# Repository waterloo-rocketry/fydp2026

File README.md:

# FYDP 2026 Electrical & Software

Sisyphus is a regeneratively cooled, 3D-printed liquid rocket engine. There are threee main electrical projects that support this system: Automedon, Achilles, and Theseus

## Automedon
Automedon is a repackaging of the team's existing EGSE stack (namely RLCS, DAQ, and GSPD) within two fully enclosed NEMA panels and with a redesigned power architecture. This vastly improves the robustness and utility of the system
Design doc: https://docs.google.com/document/d/1RASc9nuHLxcU_nNqpzqdATsLbMFS-u7HsDOORrnuTvM/edit?tab=t.0#heading=h.aovynwwb2h1r

## Achilles
Achilles, like its namesake, is designed to be an unkillable DAQ module that retains good analog performance. Unlike the team's previous COTS solutions, the system supports up to 30V common mode and differential signals, and is protected up to +/- 60V at the inputs.
DAQ v2 Design Doc (for context): https://docs.google.com/document/d/1antcjPh_7nqCMTjgXxEhXMyPKeuij0gU7g0J603f2qo/edit?tab=t.0#heading=h.4f9eymtkxact

## Theseus
Theseus is the third iteration on the team's integrated propulsion avionics PCB. It is designed to read from pressure transducers, Hall sensors, and RTDs (which are very necessary for regen testing), as well as actuating solenoid valves

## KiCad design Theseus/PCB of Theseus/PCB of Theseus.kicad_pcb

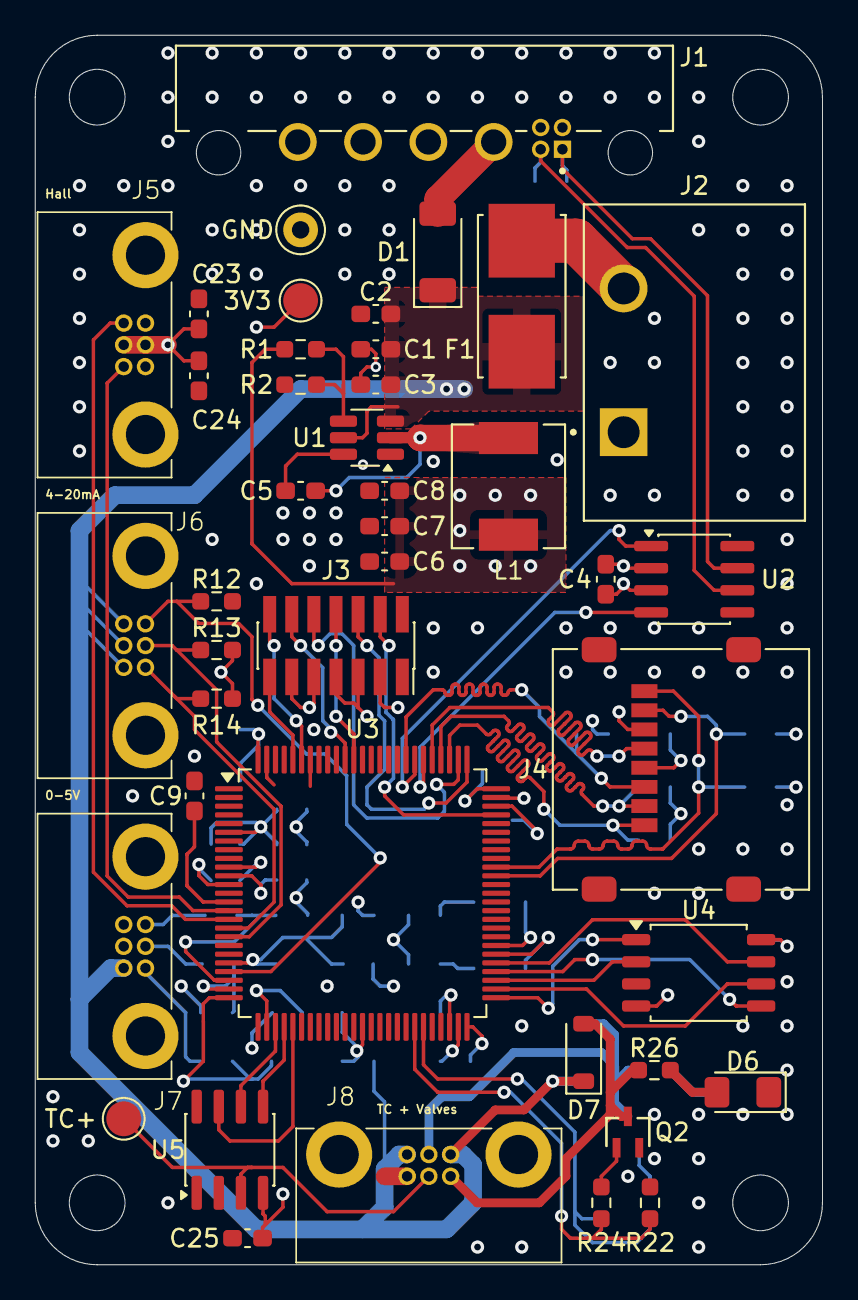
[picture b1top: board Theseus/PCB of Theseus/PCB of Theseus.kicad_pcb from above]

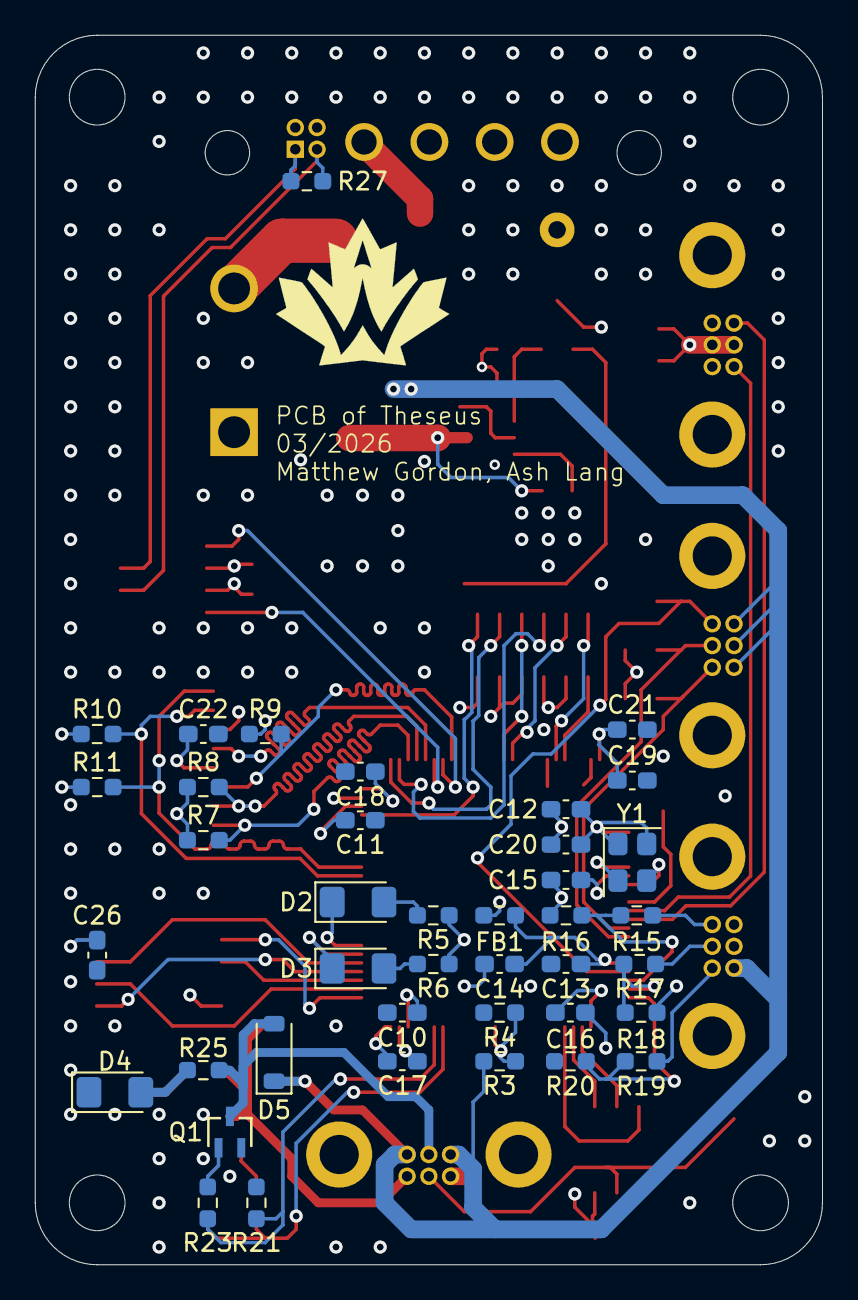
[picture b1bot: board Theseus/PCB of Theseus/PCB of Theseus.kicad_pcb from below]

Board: 4 copper layers, 45.2 x 70.6 mm, 86 parts (40 on the bottom side), 63 nets.

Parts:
3V3: TestPoint; TestPoint_Pad_D2.0mm
C1, C2, C22: 10u; C_0603_1608Metric_Pad1.08x0.95mm_HandSolder
C3, C5, C9, C12, C13, C15, C16, C17, C18, C19, C26: 100n; C_0603_1608Metric_Pad1.08x0.95mm_HandSolder
C4, C23, C24, C25: 0.1u; C_0603_1608Metric_Pad1.08x0.95mm_HandSolder
C6, C7, C8: 22u; C_0603_1608Metric_Pad1.08x0.95mm_HandSolder
C10, C11: 2.2u; C_0603_1608Metric_Pad1.08x0.95mm_HandSolder
C14: 1n; C_0603_1608Metric_Pad1.08x0.95mm_HandSolder
C20: 0.01uF; C_0603_1608Metric_Pad1.08x0.95mm_HandSolder
C21: 4.7u; C_0603_1608Metric_Pad1.08x0.95mm_HandSolder
D1: PMEG3030EP; D_SOD-128
D2: WHITE; LED_1206_3216Metric_Pad1.42x1.75mm_HandSolder
D3: BLUE; LED_1206_3216Metric_Pad1.42x1.75mm_HandSolder
D4, D6: GREEN; LED_1206_3216Metric_Pad1.42x1.75mm_HandSolder
D5, D7: CDBW140-G; D_SOD-123
F1: 0154005.DRL; FUSE_0154005.DR
FB1: PE-0603PFB121ST; R_0603_1608Metric_Pad0.98x0.95mm_HandSolder
GND: TestPoint; TestPoint_Keystone_5000-5004_Miniature
H1, H2, H3, H4: MountingHole; MountingHole_3.2mm_M3_ISO14580
J1: G125-MH104M4-04AD000P; connector_Harwin_G125-MH104M4-04AD000P
J2: 4DB-P108-02
J3: CN4 STDC14 (Programmer); PinSocket_2x07_P1.27mm_Vertical_SMD
J4: Micro SD Holder 0472192001; microSD_HC_Molex_47219-2001
J5, J6, J7, J8: Conn_01x06_Socket; connector_Harwin_G125–MG10605M4P
L1: SPM6530T-2R2M; IND_SPM6530T-2R2M
Q1, Q2: DMG1012UW-7; SOT_12UW-7_DIO
R1: 33.2k; R_0603_1608Metric_Pad0.98x0.95mm_HandSolder
R2: 10k; R_0603_1608Metric_Pad0.98x0.95mm_HandSolder
R3: 300K; R_0603_1608Metric_Pad0.98x0.95mm_HandSolder
R4: 100K; R_0603_1608Metric_Pad0.98x0.95mm_HandSolder
R5, R6: 169R; R_0603_1608Metric_Pad0.98x0.95mm_HandSolder
R7, R8, R9, R10, R11: 51k; R_0603_1608Metric_Pad0.98x0.95mm_HandSolder
R12, R13, R14: 150R ±0.1%; R_0603_1608Metric_Pad0.98x0.95mm_HandSolder
R15, R17, R19: 82K; R_0603_1608Metric_Pad0.98x0.95mm_HandSolder
R16, R18, R20: 130K; R_0603_1608Metric_Pad0.98x0.95mm_HandSolder
R21, R22: 150k; R_0603_1608Metric_Pad0.98x0.95mm_HandSolder
R23, R24: 100R; R_0603_1608Metric_Pad0.98x0.95mm_HandSolder
R25, R26: 649R; R_0603_1608Metric_Pad0.98x0.95mm_HandSolder
R27: 120R; R_0603_1608Metric_Pad0.98x0.95mm_HandSolder
TC+: TC1+; TestPoint_Pad_D2.0mm
U1: TPS565201DDC; SOT-23-6_Handsoldering
U2: TCAN334; SOIC-8_3.9x4.9mm_P1.27mm
U3: STM32H750VBTx; LQFP-100_14x14mm_P0.5mm
U4: MX25L25645G; SOIC-8_5.3x5.3mm_P1.27mm
U5: MAX6675; SOIC-8_3.9x4.9mm_P1.27mm
Y1: ASE-4.000MHz-L-C-T; Oscillator_SMD_Abracon_ASE-4Pin_3.2x2.5mm

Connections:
+3.3V: 3V3.1, C4.1, C6.1, C7.1, C8.1, C12.1, C15.1, C16.1, C17.1, C18.1, C19.1, C20.1, C21.1, C22.1, C23.1, C24.1, C25.1, C26.1, FB1.1, J3.3, J4.4 (VDD), J5.2, J5.5, L1.1, R1.1, R5.1, R6.1, R7.1, R8.1, R9.1, R10.1, R11.1, U2.3 (VCC), U3.6 (VBAT), U3.11 (VDD), U3.27 (VDD), U3.50 (VDD), U3.75 (VDD), U3.100 (VDD), U4.8 (VCC), U5.4 (Vcc), Y1.1 (EN), Y1.4 (Vdd)
+BATT: C1.1, C2.1, C3.1, D1.1 (K), D5.1 (K), D7.1 (K), F1.1, J6.4, J6.5, J6.6, J7.4, J8.1, J8.3, R3.1, U1.3 (VIN), U1.5 (EN)
/CANH: J1.1 (CANH), R27.1, U2.7 (CANH)
/CANL: J1.2 (CANL), R27.2, U2.6 (CANL)
/CAN_Rx: U2.4 (RXD), U3.81 (PD0)
/CAN_Tx: U2.1 (TXD), U3.82 (PD1)
/MCU/FLASH_MISO: U3.53 (PB14), U4.2 (SO/SIO1)
/MCU/FLASH_MOSI: U3.54 (PB15), U4.5 (SI/SIO0)
/MCU/FLASH_SCK: U3.52 (PB13), U4.6 (SCLK)
/MCU/HALL_1: J5.4, U3.15 (PC0)
/MCU/HALL_2: J5.6, U3.16 (PC1)
/MCU/LED_B: D3.1 (K), U3.56 (PD9)
/MCU/LED_W: D2.1 (K), U3.57 (PD10)
/MCU/OSC_IN: U3.12 (PH0), Y1.3 (OUT)
/MCU/PT4: R19.2, R20.1, U3.25 (PA3)
/MCU/PT5: R17.2, R18.1, U3.24 (PA2)
/MCU/PT6: R15.2, R16.1, U3.23 (PA1)
/MCU/SD_CLK: J4.5 (CLK), U3.80 (PC12)
/MCU/SD_CMD: J4.3 (CMD), R9.2, U3.83 (PD2)
/MCU/SD_D0: J4.7 (DAT0), R10.2, U3.65 (PC8)
/MCU/SD_D1: J4.8 (DAT1), R11.2, U3.66 (PC9)
/MCU/SD_D2: J4.1 (DAT2), R7.2, U3.78 (PC10)
/MCU/SD_D3: J4.2 (DAT3/CD), R8.2, U3.79 (PC11)
/MCU/TC1_MISO: U3.30 (PA6), U5.7 (SO)
/MCU/TC1_SCK: U3.29 (PA5), U5.5 (SCK)
/MCU/TCK: J3.6, U3.76 (PA14)
/MCU/TDI: J3.10, U3.77 (PA15)
/MCU/TDO: J3.8, U3.89 (PB3)
/MCU/TMS: J3.4, U3.72 (PA13)
/MCU/TRST: J3.12, U3.90 (PB4)
/MCU/VALVE_1: R21.2, R23.2, U3.45 (PE15)
/MCU/VALVE_2: R22.1, R24.2, U3.44 (PE14)
/MCU/VCP_RX: J3.13, U3.96 (PB9)
/MCU/VCP_TX: J3.14, U3.95 (PB8)
/MCU/VDDA: C13.1, C14.1, FB1.2, U3.21 (VDDA)
/MCU/V_BATT: R3.2, R4.1, U3.38 (PE8)
/MCU/~FLASH_CS: U3.51 (PB12), U4.1 (CS#)
/MCU/~FLASH_RESET: U3.55 (PD8), U4.7 (RESET#/SIO3)
/MCU/~TC1_CS: U3.28 (PA4), U5.6 (~CS)
/Valves and Sensors/PT1_OUT: J6.1, R14.1, U3.17 (PC2_C)
/Valves and Sensors/PT2_OUT: J6.2, R13.1, U3.18 (PC3_C)
/Valves and Sensors/PT3_OUT: J6.3, R12.1, U3.22 (PA0)
/Valves and Sensors/PT4_OUT: J7.1, R19.1
/Valves and Sensors/PT5_OUT: J7.2, R17.1
/Valves and Sensors/PT6_OUT: J7.3, R15.1
/Valves and Sensors/TC1+: J8.5, TC+.1, U5.3 (T+)
GND: C1.2, C2.2, C3.2, C4.2, C6.2, C7.2, C8.2, C9.2, C10.2, C11.2, C12.2, C13.2, C14.2, C15.2, C16.2, C17.2, C18.2, C19.2, C20.2, C21.2, C22.2, C23.2, C24.2, C25.2, C26.2, D4.1 (K), D6.1 (K), GND.1, J1.D (GND), J2.1, J3.5, J3.7, J3.9, J3.11, J4.6 (VSS), J4.9 (SHIELD), J5.1, J5.3, J7.6, J8.6, Q1.2 (S), Q2.2 (S), R2.2, R4.2, R12.2, R13.2, R14.2, R16.2, R18.2, R20.2, R21.1, R22.2, U1.1 (GND), U2.2 (GND), U2.5 (SHDN), U2.8 (STB), U3.10 (VSS), U3.19 (VSSA), U3.26 (VSS), U3.49 (VSS), U3.74 (VSS), U3.94 (BOOT0), U3.99 (VSS), U4.4 (GND), U5.1 (GND), U5.2 (T-), Y1.2 (GND)
unnamed: C10.1, U3.48 (VCAP)
unnamed: C11.1, U3.73 (VCAP)
unnamed: D1.2 (A), J1.A (+CHG)
unnamed: D2.2 (A), R5.2
unnamed: D3.2 (A), R6.2
unnamed: D4.2 (A), R25.1
unnamed: D5.2 (A), J8.2, Q1.3 (D), R25.2
unnamed: D6.2 (A), R26.2
unnamed: D7.2 (A), J8.4, Q2.3 (D), R26.1
unnamed: F1.2, J2.2
unnamed: Q1.1 (G), R23.1
unnamed: Q2.1 (G), R24.1
unnamed: C5.1, L1.2, U1.2 (SW)
unnamed: C5.2, U1.6 (VBST)
unnamed: R1.2, R2.1, U1.4 (VFB)
unnamed: C9.1, U3.14 (NRST)

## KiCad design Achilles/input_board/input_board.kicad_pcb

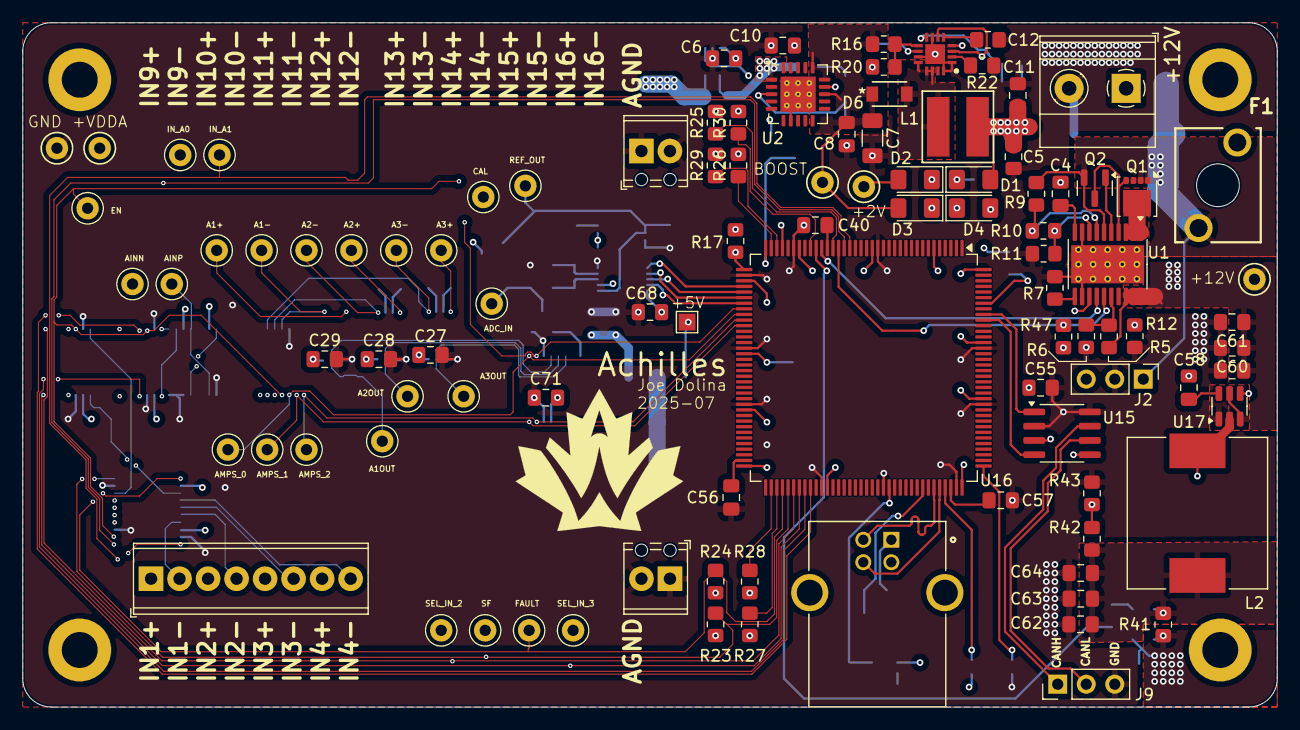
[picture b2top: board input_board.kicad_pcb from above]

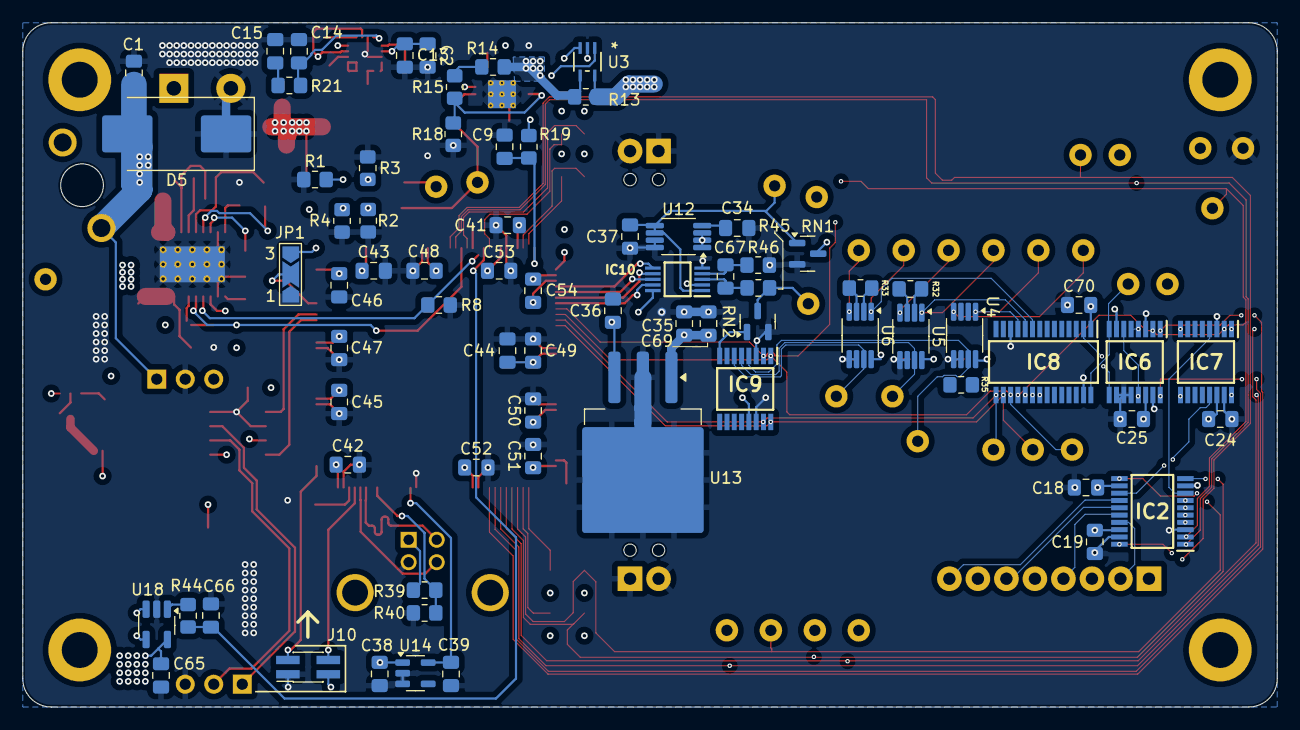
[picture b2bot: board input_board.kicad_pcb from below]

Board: 6 copper layers, 111.8 x 61.0 mm, 177 parts (73 on the bottom side), 114 nets.

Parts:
C1, C59, C60: 10uF; C_0805_2012Metric_Pad1.18x1.45mm_HandSolder
C2, C4, C13: 10nF; C_0805_2012Metric_Pad1.18x1.45mm_HandSolder
C5: 4.7uF; C_0805_2012Metric_Pad1.18x1.45mm_HandSolder
C6, C10, C12, C19, C34, C37, C38, C65, C68, C69: 1uF; C_0805_2012Metric_Pad1.18x1.45mm_HandSolder
C7: 4.7uF; C_1206_3216Metric_Pad1.33x1.80mm_HandSolder
C8, C11, C58, C61: 100nF; C_0805_2012Metric_Pad1.18x1.45mm_HandSolder
C9, C66: 1.6uF; C_0805_2012Metric_Pad1.18x1.45mm_HandSolder
C14: 300pF; C_0805_2012Metric_Pad1.18x1.45mm_HandSolder
C15: 6.8nF; C_0805_2012Metric_Pad1.18x1.45mm_HandSolder
C18, C24, C25, C27, C28, C29, C36, C70, C71: 0.1uF; C_0805_2012Metric_Pad1.18x1.45mm_HandSolder
C35: 0.33uF; C_0805_2012Metric_Pad1.18x1.45mm_HandSolder
C39: 2.2uF; C_0805_2012Metric_Pad1.18x1.45mm_HandSolder
C40, C43, C44, C45, C46, C47, C48, C49, C50, C51, C52, C53, C54: 100n; C_0805_2012Metric_Pad1.18x1.45mm_HandSolder
C41: 1u; C_0805_2012Metric_Pad1.18x1.45mm_HandSolder
C42: 4.7u; C_0805_2012Metric_Pad1.18x1.45mm_HandSolder
C55: 10u; C_0805_2012Metric_Pad1.18x1.45mm_HandSolder
C56, C57: 2.2u; C_0805_2012Metric_Pad1.18x1.45mm_HandSolder
C62, C63, C64: 22uF; C_0805_2012Metric_Pad1.18x1.45mm_HandSolder
C67: 1.1nF; C_0805_2012Metric_Pad1.18x1.45mm_HandSolder
D1: BLUE; LED_1206_3216Metric_Pad1.42x1.75mm_HandSolder
D2: GREEN; LED_1206_3216Metric_Pad1.42x1.75mm_HandSolder
D3: RED; LED_1206_3216Metric_Pad1.42x1.75mm_HandSolder
D4: WHITE; LED_1206_3216Metric_Pad1.42x1.75mm_HandSolder
D5: SMCJ36CA; D_SMC_Handsoldering
D6: B260S1F-7; CR_SOD123F_DIO
F1: 5A; 01530009Z
H1, H2, H3, H4: MountingHole_Pad; MountingHole_3.2mm_M3_DIN965_Pad
IC1: LM5157RTER; QFN50P300X300X80-17N-D
IC2: TMUX7349FPWR; SOP65P640X120-20N
IC6, IC7: MUX509IPW; SOP65P640X120-16N
IC8: MUX36D08IPW; SOP65P640X120-28N
IC9: MUX508IPW; SOP65P640X120-16N
IC10: ADS8860IDGSR; SOP50P490X110-10N
J1: Screw_Terminal_01x02; TerminalBlock_Phoenix_MKDS-1,5-2-5.08_1x02_P5.08mm_Horizont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
J2: Screw_Terminal_01x03; PinHeader_1x03_P2.54mm_Vertical
J3: Screw_Terminal_01x08; TerminalBlock_Phoenix_MPT-0,5-8-2.54_1x08_P2.54mm_Horizontal
J7, J11: Screw_Terminal_01x02; TerminalBlock_Phoenix_MPT-0,5-2-2.54_1x02_P2.54mm_Horizontal
J8: USB_B; CUI_UJ2-BH-1-TH
J9: CAN; PinHeader_1x03_P2.54mm_Vertical
J10: Programmer; PinSocket_2x02_P1.27mm_Vertical_SMD
JP1: Jumper_3_Open; SolderJumper-3_P2.0mm_Open_TrianglePad1.0x1.5mm_NumberLabels
L1: SRR5018-3R9Y; IND_BOURNS_SRR5018
L2: SRP1265A-2R2M; IND_SRP1265A-2R2M
Q1: CSD19537Q3; VSON-8_3.3x3.3mm_P0.65mm_NexFET
Q2: BSS138; SOT-23
R1: 510R; R_0805_2012Metric_Pad1.20x1.40mm_HandSolder
R2: 1.3kR; R_0805_2012Metric_Pad1.20x1.40mm_HandSolder
R3: 150R; R_0805_2012Metric_Pad1.20x1.40mm_HandSolder
R4, R19, R44: 500R; R_0805_2012Metric_Pad1.20x1.40mm_HandSolder
R5: 435kR; R_0805_2012Metric_Pad1.20x1.40mm_HandSolder
R6: 56kR; R_0805_2012Metric_Pad1.20x1.40mm_HandSolder
R7: 9.09kR; R_0805_2012Metric_Pad1.20x1.40mm_HandSolder
R8: 38.3kR; R_0805_2012Metric_Pad1.20x1.40mm_HandSolder
R9: 374kR; R_0805_2012Metric_Pad1.20x1.40mm_HandSolder
R10: 17kR; R_0805_2012Metric_Pad1.20x1.40mm_HandSolder
R11: 34kR; R_0805_2012Metric_Pad1.20x1.40mm_HandSolder
R12, R17, R18, R43, R47: 10kR; R_0805_2012Metric_Pad1.20x1.40mm_HandSolder
R13, R41: 20mR; R_0805_2012Metric_Pad1.20x1.40mm_HandSolder
R14: 203kR; R_0805_2012Metric_Pad1.20x1.40mm_HandSolder
R15: 1.29kR; R_0805_2012Metric_Pad1.20x1.40mm_HandSolder
R16: 75kR; R_0805_2012Metric_Pad1.20x1.40mm_HandSolder
R20: 2.43kR; R_0805_2012Metric_Pad1.20x1.40mm_HandSolder
R21: 1.33k; R_0805_2012Metric_Pad1.20x1.40mm_HandSolder
R22: 9.76kR; R_0805_2012Metric_Pad1.20x1.40mm_HandSolder
R23, R24, R25, R26, R27, R28, R29, R30: 1kR; R_0805_2012Metric_Pad1.20x1.40mm_HandSolder
R32: 6kR; R_0805_2012Metric_Pad1.20x1.40mm_HandSolder
R33: 1.2kR; R_0805_2012Metric_Pad1.20x1.40mm_HandSolder
R35: 122R; R_0805_2012Metric_Pad1.20x1.40mm_HandSolder
R39: 51kR; R_0805_2012Metric_Pad1.20x1.40mm_HandSolder
R40: 24kR; R_0805_2012Metric_Pad1.20x1.40mm_HandSolder
R42: 17.4kR; R_0805_2012Metric_Pad1.20x1.40mm_HandSolder
R45, R46: 15R; R_0805_2012Metric_Pad1.20x1.40mm_HandSolder
RN1: MAX5490GA01000-T; SOT-23
RN2: MAX5490TA05000-T; SOT-23
TP1: 12V; TestPoint_Keystone_5000-5004_Miniature
TP2: VBOOST; TestPoint_Keystone_5000-5004_Miniature
TP3: 2V; TestPoint_Keystone_5000-5004_Miniature
TP4: 5V; TestPoint_Pad_1.5x1.5mm
TP5: VDDA; TestPoint_Keystone_5000-5004_Miniature
TP6: GND; TestPoint_Keystone_5000-5004_Miniature
TP7: A1_OUT; TestPoint_Keystone_5000-5004_Miniature
TP8: AMP1-; TestPoint_Keystone_5000-5004_Miniature
TP9: AMP1+; TestPoint_Keystone_5000-5004_Miniature
TP10: AMP2-; TestPoint_Keystone_5000-5004_Miniature
TP11: AMP2+; TestPoint_Keystone_5000-5004_Miniature
TP12: A2_OUT; TestPoint_Keystone_5000-5004_Miniature
TP13: AMP3-; TestPoint_Keystone_5000-5004_Miniature
TP14: AMP3+; TestPoint_Keystone_5000-5004_Miniature
TP15: A3_OUT; TestPoint_Keystone_5000-5004_Miniature
TP16: REF_OUT; TestPoint_Keystone_5000-5004_Miniature
TP17: CAL; TestPoint_Keystone_5000-5004_Miniature
TP18: AINP; TestPoint_Keystone_5000-5004_Miniature
TP19: IN_A0; TestPoint_Keystone_5000-5004_Miniature
TP20: IN_A1; TestPoint_Keystone_5000-5004_Miniature
TP21: SF_1..4; TestPoint_Keystone_5000-5004_Miniature
TP22: FF_1..4; TestPoint_Keystone_5000-5004_Miniature
TP23: EN; TestPoint_Keystone_5000-5004_Miniature
TP24: AMPS0; TestPoint_Keystone_5000-5004_Miniature
TP25: AMPS1; TestPoint_Keystone_5000-5004_Miniature
TP26: AMPS2; TestPoint_Keystone_5000-5004_Miniature
TP27, TP28: AMPIN-; TestPoint_Keystone_5000-5004_Miniature
TP29: SEL_IN_2; TestPoint_Keystone_5000-5004_Miniature
TP30: SEL_IN_3; TestPoint_Keystone_5000-5004_Miniature
U1: TPS26631PWP; HTSSOP-20-1EP_4.4x6.5mm_P0.65mm_EP3.4x6.5mm_Mask2.96x2.96mm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
U2: TPS7A4701xRGW; Texas_RGW0020A_VQFN-20-1EP_5x5mm_P0.65mm_EP3.15x3.15mm_Ther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
U3: INA290A3; SC70-5_DCK_TEX
U4, U5, U6: INA849DGK; VSSOP-8_3x3mm_P0.65mm
U12: REF6050xDGK; VSSOP-8_3x3mm_P0.65mm
U13: uA7805; TO-263-3_TabPin2
U14: TPS76933; SOT-23-5
U15: MCP2562; SOIC-8_3.9x4.9mm_P1.27mm
U16: STM32H750ZBTx; LQFP-144_20x20mm_P0.5mm
U17: TPS565201; SOT-23-6
U18: INA180A3; SOT-23-5_HandSoldering

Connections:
+2V: C6.1, C41.1, C42.1, C43.1, C44.1, C45.1, C46.1, C47.1, C48.1, C49.1, C50.1, C51.1, C52.1, C53.1, C54.1, C65.1, C68.2, D3.2 (A), IC10.10 (DVDD), J10.2, JP1.3 (B), R17.1, R23.2, R24.2, R25.2, R26.2, R27.2, R28.2, R29.2, R30.2, R41.2, R47.1, TP3.1, U3.3 (VS), U15.5 (VIO), U16.6 (VBAT), U16.17 (VDD), U16.30 (VDD), U16.33 (VDDA), U16.39 (VDD), U16.52 (VDD), U16.62 (VDD), U16.72 (VDD), U16.84 (VDD), U16.108 (VDD), U16.121 (VDD), U16.131 (VDD), U16.144 (VDD), U18.4 (IN-), U18.5 (VS)
+3V3: C39.1, U14.5 (OUT), U16.95 (VDD33_USB)
+5V: C36.1, C55.1, D4.2 (A), TP4.1, U12.1 (VIN), U12.2 (EN), U12.3 (SS), U13.3 (OUT), U15.3 (VDD)
+12V: C5.1, C11.1, C38.1, C59.1, C60.1, C61.1, D1.2 (A), IC1.3 (BIAS), IC1.6 (EN/UVLO/SYNC), L1.1, R5.1, TP1.1, U1.18 (OUT), U1.19 (OUT), U1.20 (OUT), U14.1 (IN), U17.3 (VIN), U17.5 (EN)
/2V DVCC/BST: C58.2, U17.6 (VBST)
/2V DVCC/ISENSE_2V: C66.1, R44.1, U16.27 (PC1)
/12V Input/IN_SYS: C1.1, D5.2 (A2), F1.2, J2.1, Q1.1 (S), Q1.2 (S), Q1.3 (S), Q2.2 (S), R9.1, U1.6 (IN_SYS)
/12V Input/ISENSE_12V: R8.1, U1.14 (IMON), U16.26 (PC0)
/12V Input/PGTH: R5.2, R6.1, U1.16 (PGTH)
/12V Input/PWR_ON: J2.3, R12.1, U1.13 (~SHDN)
/12V Input/V_OVP: R10.2, R11.1, U1.8 (OVP)
/12V Input/V_UVLO: R9.2, R10.1, U1.7 (UVLO)
/12V Input/~FLT_12V: R47.2, U1.15 (~FLT), U16.23 (PH0)
/30V VDDA/ISENSE_30V: C9.1, R19.1, U16.36 (PA2)
/30V VDDA/PGOOD_30V: IC1.4 (PGOOD), R17.2, U16.37 (PA3)
/ADC + FVR/ADC_IN: IC9.8 (D), RN2.1 (COM1)
/ADC + FVR/CAL: IC6.7 (S4A), RN1.3 (R2), TP17.1
/ADC + FVR/CONVST: IC10.6 (CONVST), U16.40 (PA4)
/ADC + FVR/MISO: IC10.7 (DOUT), U16.42 (PA6)
/ADC + FVR/MOSI: IC10.9 (DIN), U16.43 (PA7)
/ADC + FVR/REF_OUT: C37.2, IC10.1 (REF), RN1.1 (COM1), TP16.1, U12.5 (OUT_S), U12.6 (OUT_F)
/ADC + FVR/SCK: IC10.8 (SCLK), U16.41 (PA5)
/Amplifiers/A1_OUT: IC9.4 (S1), TP7.1, U4.7
/Amplifiers/A2_OUT: IC9.5 (S2), TP12.1, U5.7
/Amplifiers/A3_OUT: IC9.6 (S3), TP15.1, U6.7
/Amplifiers/AMP1+: IC8.19 (S1A), TP9.1, U4.4 (+)
/Amplifiers/AMP1-: IC8.11 (S1B), TP8.1, U4.1 (-)
/Amplifiers/AMP2+: IC8.20 (S2A), TP11.1, U5.4 (+)
/Amplifiers/AMP2-: IC8.10 (S2B), TP10.1, U5.1 (-)
/Amplifiers/AMP3+: IC8.21 (S3A), TP14.1, U6.4 (+)
/Amplifiers/AMP3-: IC8.9 (S3B), TP13.1, U6.1 (-)
/Amplifiers/AMP_IN+: IC6.8 (DA), IC8.28 (DA), TP28.1
/Amplifiers/AMP_IN-: IC6.9 (DB), IC8.2 (DB), TP27.1
/Amplifiers/AMP_SEL_0: IC8.17 (A0), IC9.1 (A0), TP24.1, U16.45 (PC5)
/Amplifiers/AMP_SEL_1: IC8.16 (A1), IC9.16 (A1), TP25.1, U16.47 (PB1)
/Amplifiers/AMP_SEL_2: IC8.15 (A2), IC9.15 (A2), TP26.1, U16.46 (PB0)
/Frontend/EN_1..4: IC2.2 (EN), IC6.2 (EN), IC7.2 (EN), IC8.18 (EN), IC9.2 (EN), TP23.1, U16.44 (PC4)
/Frontend/FAULT_1..4: IC2.11 (FF), R24.1, TP22.1, U16.76 (PB15)
/Frontend/FAULT_5..8: R28.1, U16.74 (PB13)
/Frontend/FAULT_9..12: R26.1, U16.35 (PA1)
/Frontend/FAULT_13..16: R30.1, U16.28 (PC2_C)
/Frontend/IN1+: IC2.4 (S1A), J3.1
/Frontend/IN1-: IC2.17 (S1B), J3.2
/Frontend/IN2+: IC2.5 (S2A), J3.3
/Frontend/IN2-: IC2.16 (S2B), J3.4
/Frontend/IN3+: IC2.6 (S3A), J3.5
/Frontend/IN3-: IC2.15 (S3B), J3.6
/Frontend/IN4+: IC2.7 (S4A), J3.7
/Frontend/IN4-: IC2.14 (S4B), J3.8
/Frontend/IN+: IC6.4 (S1A), IC6.5 (S2A), IC7.8 (DA)
/Frontend/IN-: IC6.6 (S3A), IC6.13 (S1B), IC7.9 (DB)
/Frontend/INPUT_A0: IC2.1 (A0), TP19.1, U16.22 (PF10)
/Frontend/INPUT_A1: IC2.20 (A1), TP20.1, U16.21 (PF9)
/Frontend/IN_1..4+: IC2.8 (DA), IC7.4 (S1A)
/Frontend/IN_1..4-: IC2.13 (DB), IC7.13 (S1B)
/Frontend/SEL_IN_2: IC7.1 (A0), TP29.1, U16.78 (PD9)
/Frontend/SEL_IN_3: IC7.16 (A1), TP30.1, U16.79 (PD10)
/Frontend/SF_1..4: IC2.10 (SF), R23.1, TP21.1, U16.77 (PD8)
/Frontend/SF_5..8: R27.1, U16.75 (PB14)
/Frontend/SF_9..12: R25.1, U16.24 (PH1)
/Frontend/SF_13..16: R29.1, U16.34 (PA0)
/Frontend/SINGLE_DIFF_0: IC6.1 (A0), U16.81 (PD12)
/Frontend/SINGLE_DIFF_1: IC6.16 (A1), U16.80 (PD11)
/MCU/CAN_RX: U15.4 (RXD), U16.135 (PB5)
/MCU/CAN_TX: U15.1 (TXD), U16.136 (PB6)
/MCU/SWCLK: J10.3, U16.109 (PA14)
/MCU/SWDIO: J10.4, U16.105 (PA13)
/MCU/USB_D+: J8.3 (D+), U16.104 (PA12)
/MCU/USB_D-: J8.2 (D-), U16.103 (PA11)
/MCU/VBUS: J8.1 (VBUS), R39.1
/MCU/VBUS_SENSE: R39.2, R40.1, U16.101 (PA9)
GND: C1.2, C2.2, C4.2, C5.2, C6.2, C7.2, C8.2, C9.2, C10.2, C11.2, C12.2, C13.2, C14.2, C15.2, C18.2, C19.2, C24.2, C25.2, C27.2, C28.2, C29.2, C34.1, C35.2, C36.2, C37.1, C38.2, C39.2, C40.2, C41.2, C42.2, C43.2, C44.2, C45.2, C46.2, C47.2, C48.2, C49.2, C50.2, C51.2, C52.2, C53.2, C54.2, C55.2, C56.2, C57.2, C59.2, C60.2, C61.2, C62.2, C63.2, C64.2, C65.2, C66.2, C68.1, C69.1, C70.1, C71.1, D5.1 (A1), IC1.1 (PGND_1), IC1.7 (AGND), IC1.11 (MODE), IC1.16 (PGND_2), IC1.17 (EP), IC2.3 (VSS), IC2.9 (VFN), IC2.19 (GND), IC6.3 (VSS), IC6.10 (S4B), IC6.11 (S3B), IC6.12 (S2B), IC6.15 (GND), IC7.3 (VSS), IC7.15 (GND), IC8.12 (GND), IC8.27 (VSS), IC9.3 (VSS), IC9.14 (GND), IC10.5 (GND), J1.2, J2.2, J7.1, J7.2, J8.4 (GND), J9.3, J10.1, J11.1, J11.2, JP1.1 (A), R1.2, R2.2, R3.2, R4.2, R6.2, R7.2, R8.2, R11.2, R12.2, R18.2, R20.2, R22.1, R40.2, R43.2, R46.2, RN1.2 (R1), RN2.2 (R1), TP6.1, U1.9 (GND), U1.12 (MODE), U1.21 (GND), U2.7 (GND), U2.21 (EP), U3.2 (GND), U4.5 (Vs-), U4.6 (Ref), U5.5 (Vs-), U5.6 (Ref), U6.5 (Vs-), U6.6 (Ref), U12.7 (GND_F), U12.8 (GND_S), U13.2 (GND), U14.2 (GND), U14.3 (~EN), U15.2 (VSS), U15.8 (STBY), U16.16 (VSS), U16.31 (VSSA), U16.38 (VSS), U16.51 (VSS), U16.61 (VSS), U16.83 (VSS), U16.94 (VSS), U16.107 (VSS), U16.120 (VSS), U16.130 (VSS), U17.1 (GND), U18.2 (GND)
unnamed: C15.1, R21.1
unnamed: C56.1, U16.71 (VCAP)
unnamed: C57.1, U16.106 (VCAP)
unnamed: D1.1 (K), R1.1
unnamed: D2.1 (K), R2.1
unnamed: D3.1 (K), R3.1
unnamed: D4.1 (K), R4.1
unnamed: D6.2 (A), IC1.12 (SW_1), IC1.13 (SW_2), IC1.14 (SW_3), L1.2
unnamed: C14.1, IC1.8 (COMP), R21.2
unnamed: IC1.9 (FB), R16.2, R20.1
unnamed: IC1.5 (RT), R22.2
unnamed: C2.1, C13.1, IC1.10 (SS)
unnamed: C12.1, IC1.2 (VCC)
unnamed: C67.1, IC10.4 (AINN), R46.1
unnamed: C67.2, IC10.3 (AINP), R45.2
unnamed: F1.1, J1.1
unnamed: J9.1, U15.7 (CANH)
unnamed: J9.2, U15.6 (CANL)
unnamed: JP1.2 (C), U16.138 (BOOT0)
unnamed: Q1.5 (D), U1.1 (IN), U1.2 (IN), U1.3 (IN)
unnamed: Q1.4 (G), Q2.3 (D), U1.4 (B_GATE)
unnamed: Q2.1 (G), U1.5 (DRV)
unnamed: R14.2, R15.1
unnamed: R32.1, U5.2 (Rg)
unnamed: R32.2, U5.3 (Rg)
unnamed: R33.1, U6.2 (Rg)
unnamed: R33.2, U6.3 (Rg)
unnamed: R45.1, RN2.3 (R2), TP18.1
unnamed: R7.1, U1.11 (ILIM)
unnamed: C4.1, U1.10 (dVdT)
unnamed: C10.1, U2.14 (NR)
unnamed: R15.2, R18.1, U2.3 (SENSE/FB)
unnamed: R13.1, R14.1, U2.1 (OUT), U2.20 (OUT), U3.4 (IN+)
unnamed: R19.2, U3.1 (VO)
unnamed: C34.2, U12.4 (FILT)
unnamed: C40.1, U16.25 (NRST)
unnamed: C58.1, L2.1, U17.2 (SW)
unnamed: R42.2, R43.1, U17.4 (VFB)
unnamed: C62.1, C63.1, C64.1, L2.2, R41.1, R42.1, U18.3 (IN+)
unnamed: R44.2, U18.1 (VO)
VDDA: C18.1, C19.1, C24.1, C25.1, C27.1, C28.1, C29.1, C35.1, C69.2, C70.2, C71.2, IC2.12 (VFP), IC2.18 (VDD), IC6.14 (VDD), IC7.14 (VDD), IC8.1 (VDD), IC9.13 (VDD), IC10.2 (AVDD), R13.2, TP5.1, U3.5 (IN-), U4.8 (Vs+), U5.8 (Vs+), U6.8 (Vs+), U13.1 (IN)
V_BOOST: C7.1, C8.1, D2.2 (A), D6.1 (K), R16.1, TP2.1, U2.13 (EN), U2.15 (IN), U2.16 (IN)

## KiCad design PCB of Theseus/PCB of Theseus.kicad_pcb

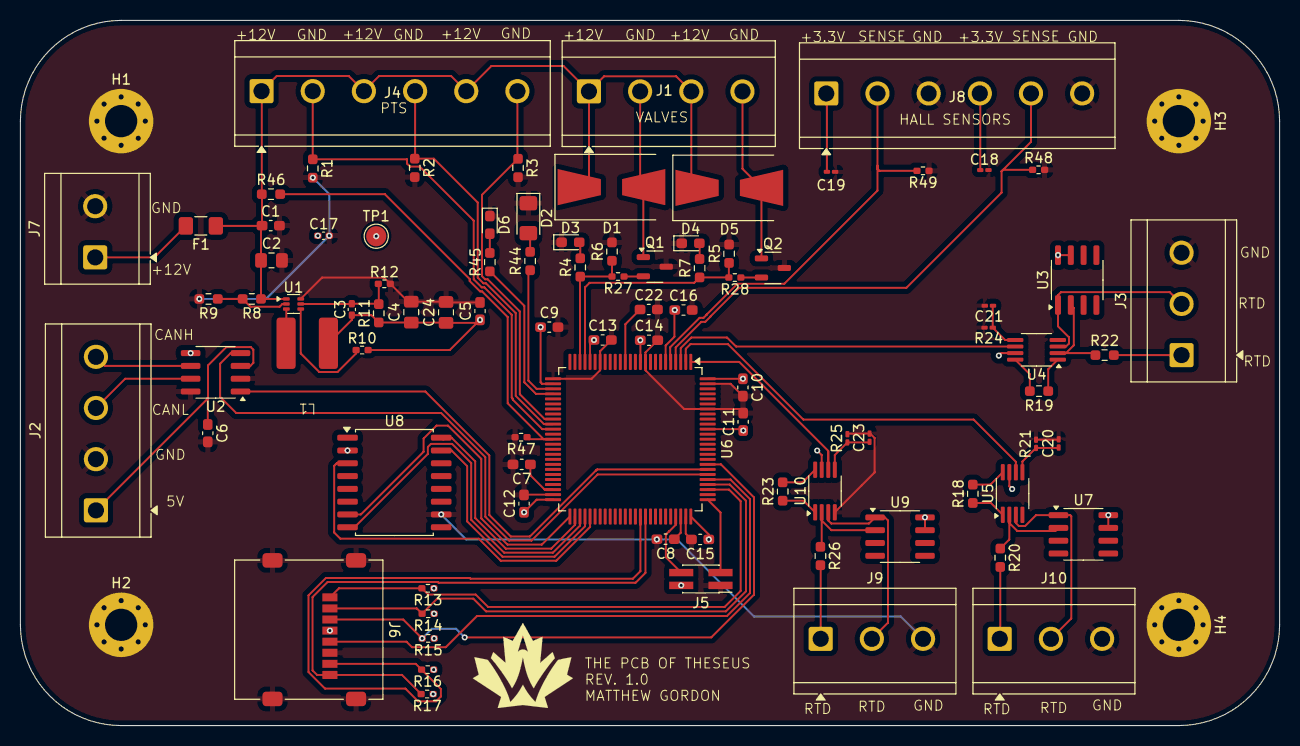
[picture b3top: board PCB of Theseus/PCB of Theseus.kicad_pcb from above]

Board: 2 copper layers, 125.0 x 70.0 mm, 93 parts (0 on the bottom side), 68 nets.

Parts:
C1, C5: 100nF; C_0603_1608Metric_Pad1.08x0.95mm_HandSolder
C2, C4, C24: 22uF; C_0805_2012Metric_Pad1.18x1.45mm_HandSolder
C3: 10pF; C_0402_1005Metric_Pad0.74x0.62mm_HandSolder
C6: 10u; C_0603_1608Metric_Pad1.08x0.95mm_HandSolder
C7, C8: 2.2u; C_0603_1608Metric_Pad1.08x0.95mm_HandSolder
C9, C10, C11, C12, C13, C14, C15, C22: 100n; C_0603_1608Metric_Pad1.08x0.95mm_HandSolder
C16: 4.7u; C_0603_1608Metric_Pad1.08x0.95mm_HandSolder
C17: 1u; C_0402_1005Metric_Pad0.74x0.62mm_HandSolder
C18, C19: 0.1uF; C_0201_0603Metric_Pad0.64x0.40mm_HandSolder
C20, C21, C23: 510pF; C_0201_0603Metric_Pad0.64x0.40mm_HandSolder
D1, D5: D; D_SMB-SMC_Universal_Handsoldering
D2: WHITE; D_1206_3216Metric_Pad1.42x1.75mm_HandSolder
D3, D4: GREEN; D_0603_1608Metric_Pad1.05x0.95mm_HandSolder
D6: BLUE; D_0603_1608Metric_Pad1.05x0.95mm_HandSolder
F1: TBD; Fuse_1206_3216Metric_Pad1.42x1.75mm_HandSolder
H1, H2, H3, H4: MountingHole_3.2mm_M3_Pad_Via
J1, J2: Screw_Terminal_01x04; TerminalBlock_CUI_TB007-508-04_1x04_P5.08mm_Horizontal
J3, J9, J10: Screw_Terminal_01x03; TerminalBlock_CUI_TB007-508-03_1x03_P5.08mm_Horizontal
J4, J8: Screw_Terminal_01x06; TerminalBlock_CUI_TB007-508-06_1x06_P5.08mm_Horizontal
J5: Programmer; PinHeader_2x02_P1.27mm_Vertical_SMD
J6: Micro_SD_Card; microSD_HC_Molex_47219-2001
J7: Screw_Terminal_01x02; TerminalBlock_CUI_TB007-508-02_1x02_P5.08mm_Horizontal
L1: 3.3uH; VLS6045EX-3R3N
Q1, Q2: NMOS; SOT-23-3
R1, R2, R3: 150R; R_0603_1608Metric_Pad0.98x0.95mm_HandSolder
R4, R7, R44, R45: 169R; R_0603_1608Metric_Pad0.98x0.95mm_HandSolder
R5, R6: 150k; R_0603_1608Metric_Pad0.98x0.95mm_HandSolder
R8: 221k; R_0603_1608Metric_Pad0.98x0.95mm_HandSolder
R9: 30k; R_0603_1608Metric_Pad0.98x0.95mm_HandSolder
R10, R12: 10k; R_0402_1005Metric_Pad0.72x0.64mm_HandSolder
R11: 45.3k; R_0603_1608Metric_Pad0.98x0.95mm_HandSolder
R13, R14, R15, R16, R17: 50k; R_0402_1005Metric_Pad0.72x0.64mm_HandSolder
R18, R19, R23: 2k; R_0603_1608Metric_Pad0.98x0.95mm_HandSolder
R20, R22, R26: 76.8R; R_0603_1608Metric_Pad0.98x0.95mm_HandSolder
R21, R24, R25: 324k; R_0201_0603Metric_Pad0.64x0.40mm_HandSolder
R27, R28: 1k; R_0402_1005Metric_Pad0.72x0.64mm_HandSolder
R46: 30K; R_0603_1608Metric_Pad0.98x0.95mm_HandSolder
R47: 10K; R_0402_1005Metric_Pad0.72x0.64mm_HandSolder
R48, R49: 3.4k; R_0402_1005Metric_Pad0.72x0.64mm_HandSolder
TP1: TestPoint; TestPoint_Pad_D2.0mm
U1: TPS564257DRL; SOT-563
U2: MCP2562; SOIC-8_3.9x4.9mm_P1.27mm
U3, U7, U9: REF200; SOIC-8_3.9x4.9mm_P1.27mm
U4, U5, U10: INA326; MSOP-8_3x3mm_P0.65mm
U6: STM32H750VBTx; LQFP-100_14x14mm_P0.5mm
U8: MX25L25645G; SOIC-16W_7.5x10.3mm_P1.27mm

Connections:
+3.3V: C3.1, C4.1, C5.1, C9.1, C10.1, C11.1, C12.1, C13.1, C14.1, C15.1, C16.1, C17.1, C18.1, C19.1, C24.1, J5.2, J6.4 (VDD), J8.1, J8.4, L1.1, R10.2, R11.1, R13.1, R14.1, R15.1, R16.1, R17.1, TP1.1, U2.5 (VIO), U3.7 (I2_HIGH), U3.8 (I1_HIGH), U4.7 (V+), U5.7 (V+), U6.6 (VBAT), U6.11 (VDD), U6.21 (VDDA), U6.27 (VDD), U6.50 (VDD), U6.75 (VDD), U6.90 (PB4), U6.100 (VDD), U7.7 (I2_HIGH), U7.8 (I1_HIGH), U8.2 (VCC), U9.7 (I2_HIGH), U9.8 (I1_HIGH), U10.7 (V+)
+5V: C6.1, J2.1, U2.3 (VDD)
+BATT: C1.1, C2.1, D1.1 (K), D5.1 (K), F1.1, J1.1, J1.3, J4.1, J4.3, J4.5, R8.1, R46.1, U1.1 (Vin)
/CANH: J2.3, U2.7 (CANH)
/CANL: J2.4, U2.6 (CANL)
/CAN_Rx: U2.4 (RXD), U6.81 (PD0)
/CAN_Tx: U2.1 (TXD), U6.82 (PD1)
/MCU/HALL_1: J8.2, R49.2, U6.5 (PE6)
/MCU/HALL_2: J8.5, R48.1, U6.4 (PE5)
/MCU/LED_BLUE: R44.1, U6.28 (PA4)
/MCU/LED_RED: R45.1, U6.29 (PA5)
/MCU/MEM_~RESET: U6.55 (PD8), U8.3 (RESET#)
/MCU/PT_1: J4.2, R1.1, U6.36 (PB2)
/MCU/PT_2: J4.4, R2.1, U6.35 (PB1)
/MCU/PT_3: J4.6, R3.1, U6.34 (PB0)
/MCU/RTD_1: U4.6, U6.3 (PE4)
/MCU/RTD_2: U5.6, U6.2 (PE3)
/MCU/RTD_3: U6.1 (PE2), U10.6
/MCU/SD_CLK: J6.5 (CLK), U6.80 (PC12)
/MCU/SD_CMD: J6.3 (CMD), R15.2, U6.83 (PD2)
/MCU/SD_D0: J6.7 (DAT0), R16.2, U6.65 (PC8)
/MCU/SD_D1: J6.8 (DAT1), R17.2, U6.66 (PC9)
/MCU/SD_D2: J6.1 (DAT2), R13.2, U6.78 (PC10)
/MCU/SD_D3: J6.2 (DAT3/CD), R14.2, U6.79 (PC11)
/MCU/SPI_MISO: U6.53 (PB14), U8.8 (SO/SIO1)
/MCU/SPI_MOSI: U6.54 (PB15), U8.15 (SI/SIO0)
/MCU/SPI_NSS: U6.51 (PB12), U8.7 (CS#)
/MCU/SPI_SCK: U6.52 (PB13), U8.16 (SCLK)
/MCU/SWCLK: J5.3, U6.76 (PA14)
/MCU/SWDIO: J5.4, U6.72 (PA13)
/MCU/VALVE_1: R4.1, R6.1, R27.2, U6.23 (PA1)
/MCU/VALVE_2: R5.1, R7.1, R28.2, U6.22 (PA0)
/MCU/V_BATT: R46.2, R47.1, U6.38 (PE8)
GND: C1.2, C2.2, C4.2, C5.2, C6.2, C7.2, C8.2, C9.2, C10.2, C11.2, C12.2, C13.2, C14.2, C15.2, C16.2, C17.2, C18.2, C19.2, C20.2, C21.2, C22.2, C23.2, C24.2, D2.1 (K), D3.1 (K), D4.1 (K), D6.1 (K), H1.1, H2.1, H3.1, H4.1, J2.2, J3.3, J5.1, J6.6 (VSS), J6.9 (SHIELD), J7.2, J8.3, J8.6, J9.3, J10.3, Q1.3 (S), Q2.3 (S), R1.2, R2.2, R3.2, R5.2, R6.2, R9.2, R12.2, R21.2, R24.2, R25.2, R47.2, R48.2, R49.1, U1.6 (GND), U2.2 (VSS), U2.8 (STBY), U4.4 (V-), U5.4 (V-), U6.10 (VSS), U6.19 (VSSA), U6.26 (VSS), U6.49 (VSS), U6.74 (VSS), U6.94 (BOOT0), U6.99 (VSS), U8.10 (GND), U10.4 (V-)
unnamed: C7.1, U6.48 (VCAP)
unnamed: C8.1, U6.73 (VCAP)
unnamed: D1.2 (A), J1.2, Q1.1 (D)
unnamed: D2.2 (A), R44.2
unnamed: D3.2 (A), R4.2
unnamed: D4.2 (A), R7.2
unnamed: D5.2 (A), J1.4, Q2.1 (D)
unnamed: D6.2 (A), R45.2
unnamed: J3.1, R22.2
unnamed: J3.2, U3.1 (I1_LOW), U4.3 (+)
unnamed: F1.2, J7.1
unnamed: J9.1, R26.2
unnamed: J9.2, U9.1 (I1_LOW), U10.3 (+)
unnamed: J10.1, R20.2
unnamed: J10.2, U5.3 (+), U7.1 (I1_LOW)
unnamed: Q1.2 (G), R27.1
unnamed: Q2.2 (G), R28.1
unnamed: R18.1, U5.1 (R1)
unnamed: R18.2, U5.8 (R1)
unnamed: R19.1, U4.1 (R1)
unnamed: R19.2, U4.8 (R1)
unnamed: R23.1, U10.1 (R1)
unnamed: R23.2, U10.8 (R1)
unnamed: R8.2, R9.1, U1.2 (EN)
unnamed: C3.2, R11.2, R12.1, U1.5 (FB)
unnamed: R10.1, U1.4 (PG)
unnamed: L1.2, U1.3 (SW)
unnamed: R22.1, U3.2 (I2_LOW), U4.2 (-)
unnamed: C21.1, R24.1, U4.5 (R2)
unnamed: R20.1, U5.2 (-), U7.2 (I2_LOW)
unnamed: C20.1, R21.1, U5.5 (R2)
unnamed: C22.1, U6.14 (NRST)
unnamed: R26.1, U9.2 (I2_LOW), U10.2 (-)
unnamed: C23.1, R25.1, U10.5 (R2)

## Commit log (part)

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2025-09-10 Updates to the RTD sensing circuit, added flash memory to the schematic.
2025-09-13 Updates to schematic, added 3rd RTD, initial PCB layout completed.
2025-09-20 Move theseus to subfolder
2025-09-20 Add automedon files
2025-09-20 Add Achilles
2025-09-22 Add Theseus current version?
2025-10-02 test version PCB
2025-10-02 Theseus_Dev_Rev2
    It's still the same PCB
2025-10-02 Minor routing changes
    Still the same PCB
2025-10-07 Fixes V3
    - Copied Ferrite Bead P/N from processor
    - Added external oscillator
    - Made status LED pins pull-down
    - Copied processor programming header
2025-10-10 NMOS and Diode Update
    Updated Diode and NMOS to support 1A max. Fixed valve state LED to draw from BATT instead of MCU.
2025-10-15 Update KiCad schematics and add power converter library
2025-10-18 Updated schematics and symbols based on feedback
2025-10-19 Resize boost caps in sim; update pcb with PNs
2025-10-20 Update power schematic (power.kicad_sch)
2025-10-22 Update eth subsheet
2025-10-22 Update bunch of other stuff - dont touch power
2025-10-22 updated cb1 and f1 on schematic
2025-10-22 Minor power path changes
2025-10-23 Relabel 12V
2025-10-23 Revert other files to main
2025-10-23 Move power symbols into main sym lib
2025-10-26 Update eth ports
2025-10-31 Update connector
2025-11-03 Revert "Update connector"
    This reverts commit 3a37b6a19b99deb2b7118eab30d8044c58bd28a2.
2025-11-14 Update a bunch of shit
2025-11-23 Fix DAQ
2026-03-15 change CAN transciever to 3v3, add lipo charging, change PT connectors, tidy schematic
2026-03-15 Fix PT3 ADC
    Updated PT3 to use valid ADC pin
2026-03-15 Flight design, first pass
2026-03-15 Flight design v1
    First pass at flight design
2026-03-15 10-MAR-2026 Revisions
2026-03-15 10 MAR 2026 Changes pt 2
2026-03-17 layout and routing + minor schematic changes
2026-03-17 minor fixes, generate prod files + reference files
2026-03-19 final 3d model + pdf
